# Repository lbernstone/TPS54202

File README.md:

# TPS54202
=========

A kicad layout for a 3V3 DC power supply based on TPS54202, suitable for import into another project.  Also includes a spreadsheet to calculate resistors needed for different voltages and overvoltage protection.

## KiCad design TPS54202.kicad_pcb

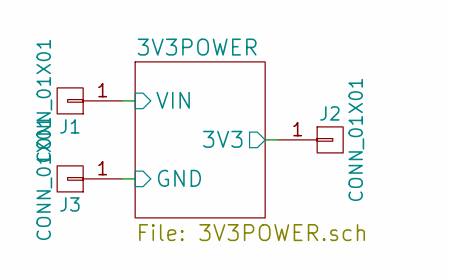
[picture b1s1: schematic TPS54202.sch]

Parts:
J1, J2, J3: CONN_01X01; Socket_Strip_Straight_1x01_Pitch2.54mm

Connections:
/3V3POWER/3V3: J2.1; also elsewhere on the board
/3V3POWER/GND: J3.1; also elsewhere on the board
/3V3POWER/VIN: J1.1; also elsewhere on the board

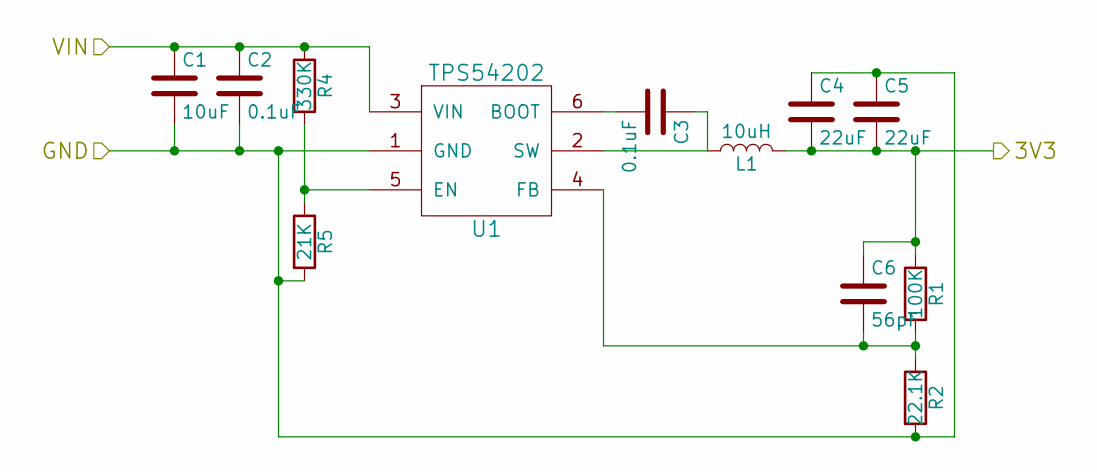
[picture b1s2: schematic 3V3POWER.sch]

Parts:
C1: 10uF; C_0805
C2, C3: 0.1uF; C_0805
C4, C5: 22uF; C_0805
C6: 56pF; C_0805
L1: 10uH; C_1812
R1: 100K; R_0805
R2: 22.1K; R_0805
R4: 330K; R_0805
R5: 21K; R_0805
U1: TPS54202; SOT-23-6

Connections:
/3V3POWER/3V3: C4.2, C5.2, C6.1, L1.2, R1.1; also elsewhere on the board
/3V3POWER/GND: C1.2, C2.2, C4.1, C5.1, R2.2, R5.2, U1.1 (GND); also elsewhere on the board
/3V3POWER/VIN: C1.1, C2.1, R4.1, U1.3 (VIN); also elsewhere on the board
unnamed: C3.1, L1.1, U1.2 (SW)
unnamed: C3.2, U1.6 (BOOT)
unnamed: C6.2, R1.2, R2.1, U1.4 (FB)
unnamed: R4.2, R5.1, U1.5 (EN)

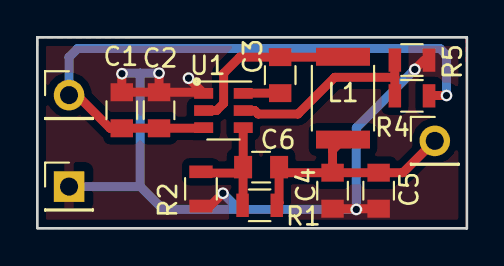
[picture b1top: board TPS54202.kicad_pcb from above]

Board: 2 copper layers, 23.9 x 10.6 mm, 15 parts (0 on the bottom side), 7 nets.

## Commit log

2018-01-01 added an image of the board
